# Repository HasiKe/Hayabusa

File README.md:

# Hayabusa

Eigenbau-Motorsteuerung und Umbauprojekte für die Suzuki Hayabusa der ersten
Generation (1999–2007).

Das Repository enthält die Elektronik des Umbaus: Schaltpläne und Layouts der
Steuergeräte, die Firmware, die Abstimmung und die Dokumentation dazu. Die
Speeduino-Firmware ist dabei der Ausgangspunkt, nicht das Ergebnis — Platinen,
Sensorik und die Motorrad-spezifischen Funktionen sind eigene Arbeit.

---

## Inhalt

| Pfad | Inhalt |
|---|---|
| [`hardware/ECU/`](hardware/ECU) | Steuergerät: Schaltplan, Layout, Fertigungsdaten, Gehäuse |
| [`speeduino/`](https://github.com/HasiKe/speeduino/tree/Hayabusa/ECU-R3) | Motorsteuerungs-Firmware und Sensor-Modul-Firmware, Submodul auf den eigenen Fork |
| [`hardware/exhaust-mic/`](hardware/exhaust-mic) | Zweikanalige Tonaufnahme von Motor und Auspuff |
| [`tune/`](tune) | TunerStudio-Projekt [`Hayabusa-R3`](tune/Hayabusa-R3) (generiert aus den Serienkennfeldern in `tune/setup/`) |
| [`docs/`](docs) | Dokumentation und Spezifikationen |

---

## Das Steuergerät

Ersetzt das Seriensteuergerät vollständig. Zweilagige Platine von rund
148 × 112 mm mit einem Teensy 4.1 als Rechenkern, Schaltplanstand
**Revision 3.0 (Entwurf)**.

### Leistungsteil

| Baustein | Aufgabe |
|---|---|
| MC33810 | Einspritzung und Zündung über SPI, vier Kanäle je Pfad |
| 4× ISL9V5036 | Zünd-IGBTs an den Gate-Treibern des MC33810 |
| 3× ZXMS6006 | Low-Side für Kraftstoffpumpe, Lüfter, Starter, Drehzahlmesser, FI-Lampe |
| 2× BTF3050TE | High-Side für Ladedrucksteller und Lambdaheizung, mit Stromfühler |
| DRV8434A | Schrittmotor für den Leerlaufsteller |

### Signalaufbereitung

| Baustein | Aufgabe |
|---|---|
| MAX9926 | Zwei Kanäle Induktivgeber für Kurbelwelle und Nockenwelle |
| TPIC8101 | Klopfsensor mit programmierbarem Bandpass und Integrator |
| LMV324 | Puffer für Lambda, Komparator für den Kippschalter |
| SP720 / BAV199 | Klemmung sämtlicher Sensoreingänge |

### Versorgung und Infrastruktur

| Baustein | Aufgabe |
|---|---|
| LM74700 + SQM120N06 | Verpolschutz als aktive Diode |
| TPS54360B | Abwärtswandler auf 5 V, automotive-tauglich |
| TPS3823 | Externer Watchdog, verriegelt bei Ausfall die Endstufen |
| W25Q32 | SPI-Flash als Kennfeldspeicher |
| MCP2562 | CAN zum Sensor-Modul und zum Cockpit |
| ADXL343 | Beschleunigungssensor, bestückt, softwareseitig ungenutzt |

Vollständige Pinbelegung, Kalibrierhinweise und die offenen Punkte der
Revision 3.0: **[HAYABUSA_ECU_R3.md](https://github.com/HasiKe/speeduino/blob/Hayabusa/ECU-R3/HAYABUSA_ECU_R3.md)**

---

## Firmware

Fork von [Speeduino](https://github.com/speeduino/speeduino), Branch
[`Hayabusa/ECU-R3`](https://github.com/HasiKe/speeduino/tree/Hayabusa/ECU-R3),
eingebunden als Submodul.

```bash
git submodule update --init
cd speeduino && pio run -e teensy41_hayabusa
```

In TunerStudio Board **57 „Gen1 Hayabusa ECU R3"** wählen.

Was über den Serienstand von Speeduino hinausgeht:

- **Vier umschaltbare Kennfeldsätze** für Kraftstoff, Zündung und Ladedruck.
  Auswahl beim Einschalten über Kupplung und Vollgas, Rückmeldung über
  FI-Lampe und Drehzahlmesser.
- **Klopfregelung** mit dem TPIC8101: Konfiguration über SPI,
  Integrationsfenster am Zündfunken, Auswertung über Speeduinos
  Zündrücknahme.
- **Externer Watchdog**, der nur bedient wird, solange die Hauptschleife
  läuft — bleibt sie hängen, fallen Einspritzung und Zündung ab.
- **Motorrad-Ein- und Ausgänge**: Neutral, Kupplung, Gangsensor,
  Kippschalter, FI-Lampe, Lambdaheizung.
- **Kanalzuordnung nach Zündfolge 1-2-4-3** am Serienstecker, der nach
  Zylindern belegt ist.
- **Kennfelder im SPI-Flash** statt in der EEPROM-Emulation des Teensy, die
  für vier Sätze zu klein ist.

---

## Sensor-Modul

Zweite Platine, 120 × 64 mm, eigener STM32G474. Nimmt der Motorsteuerung alles
ab, was langsam ist, und meldet es über CAN.

- vier Abgastemperaturen über MAX31855K-Thermoelementwandler
- Öldruck, Kraftstoffdruck, Abgasdruck, Öltemperatur
- zwei Wassertemperaturen im Ladeluftkühlerkreis
- Quickshifter-Geber
- Regelung des Ladeluftkühler-Lüfters, lokal und damit unabhängig vom CAN-Bus

Firmware, CAN-Protokoll und die Zuordnung zu Speeduinos Eingangskanälen:
[`speeduino/sensor-module/README.md`](https://github.com/HasiKe/speeduino/blob/Hayabusa/ECU-R3/sensor-module/README.md)

---

## Exhaust-Mic

Eigenständiges Projekt: zweikanalige Tonaufnahme von Motor- und
Auspuffgeräuschen. Zwei Mikrofonköpfe mit 135 dBSPL Grenzschalldruck an einem
24-bit-Stereo-ADC, aufgezeichnet von einem ESP32-S3 auf microSD, mit
Zeitstempeln zur Synchronisation mit Videomaterial.

Schaltpläne, Layout, Gehäuse und Firmware entstehen aus Python-Generatoren —
Pinbelegung und Netznamen stehen dadurch nur an einer Stelle.

Eigenes Repository, hier als Submodul eingebunden:
[HasiKe/Exhaust-Mic](https://github.com/HasiKe/Exhaust-Mic)

---

## Stand

| Bereich | Stand |
|---|---|
| Steuergerät, Schaltplan | Revision 3.0 im Entwurf, Revision 1 gefertigt |
| Steuergerät, Firmware | Läuft, auf aktuellem Speeduino-Stand |
| Sensor-Modul, Hardware | Revision 3.0 im Entwurf |
| Sensor-Modul, Firmware | Übersetzt, noch nicht am Fahrzeug erprobt |
| Exhaust-Mic | Schaltplan und Layout fertig, Fertigung offen |
| Grundabstimmung | Erststart-Tune erzeugt (`tune/Hayabusa-R3`), Motor damit noch nicht gelaufen |

Was vor dem ersten Start geprüft werden muss — Trigger-Winkel, Kalibrierungen,
Kanalzuordnung, Polarität des Kippschalters, Klopfschwellen — steht in
[`tune/Hayabusa-R3/README.md`](tune/Hayabusa-R3/README.md),
[HAYABUSA_ECU_R3.md](https://github.com/HasiKe/speeduino/blob/Hayabusa/ECU-R3/HAYABUSA_ECU_R3.md)
und im [README des Sensor-Moduls](https://github.com/HasiKe/speeduino/blob/Hayabusa/ECU-R3/sensor-module/README.md).

---

## Dokumentation

| Dokument | Inhalt |
|---|---|
| [HARDWARE.md](docs/HARDWARE.md) | Platinen, Steckerbelegung, mechanische Daten |
| [SOFTWARE.md](docs/SOFTWARE.md) | Firmware-Aufbau, Build, Codestruktur |
| [INSTALLATION.md](docs/INSTALLATION.md) | Einbau, Verkabelung, Inbetriebnahme |
| [TUNING.md](docs/TUNING.md) | Kennfelder, Kalibrierung, Abstimmung |
| [PROJECT_STRUCTURE.md](docs/PROJECT_STRUCTURE.md) | Aufbau des Repositories |
| [CHANGELOG.md](CHANGELOG.md) | Versionshistorie |

Externe Quellen: [Speeduino-Wiki](https://wiki.speeduino.com) ·
[Speeduino-Forum](https://speeduino.com/forum) ·
[TunerStudio](http://tunerstudio.com)

---

## Lizenz

Die Firmware im Submodul steht unter GPL v3, wie Speeduino selbst. Hardware
und Dokumentation stehen unter CC BY-SA 4.0. Fremdsoftware liegt nicht im
Repository, sondern wird bei Bedarf aus der jeweiligen Quelle geladen.

## Haftungsausschluss

Ein selbst gebautes Steuergerät greift in Zündung und Kraftstoffzufuhr ein.
Fehler darin führen zu Motorschaden oder zum Ausfall während der Fahrt. Der
Nachbau erfolgt auf eigene Verantwortung, und im Geltungsbereich der StVZO
erlischt mit solchen Eingriffen die Betriebserlaubnis, solange kein Gutachten
vorliegt.

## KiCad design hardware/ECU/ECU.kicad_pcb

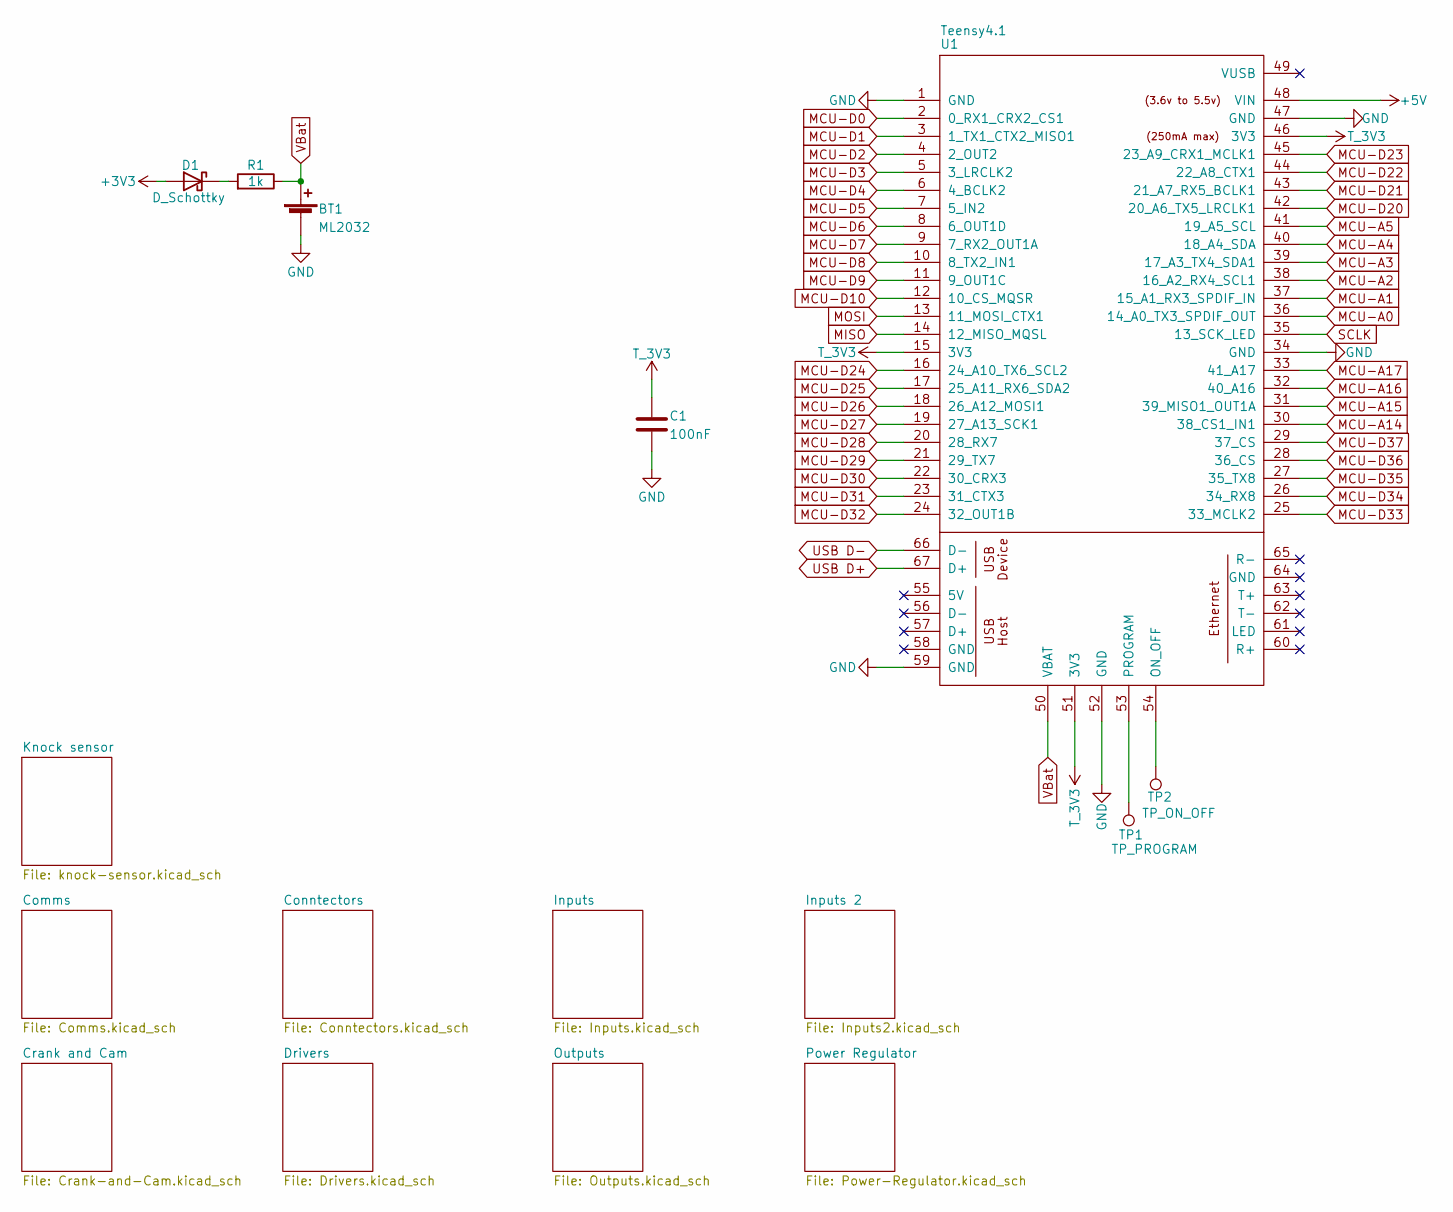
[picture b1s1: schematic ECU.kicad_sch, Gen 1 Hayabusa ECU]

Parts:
BT1: ML2032; BatteryHolder_Keystone_3034_1x20mm; Manufacturer_Part_Number 3034; Digikey Part Number 36-3034-ND
C1: 100nF; C_0805_2012Metric; Manufacturer_Part_Number CC0805KRX7R9BB104; Digikey Part Number 311-1140-1-ND
D1: D_Schottky; D_PowerDI-123; Manufacturer_Part_Number DFLS240-7; Digikey Part Number DFLS240-7DICT-ND
R1: 1k; R_0805_2012Metric; Manufacturer_Part_Number RC0805FR-071KL; Digikey Part Number 311-1.00KCRCT-ND
TP1: TP_PROGRAM; TestPoint_Pad_D1.5mm
TP2: TP_ON_OFF; TestPoint_Pad_D1.5mm
U1: Teensy4.1; Teensy41; Manufacturer_Part_Number DEV-16771; Digikey Part Number 1568-16771-ND

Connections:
+3V3: D1.2 (A); also elsewhere on the board
+5V: U1.48 (VIN); also elsewhere on the board
GND: BT1.2 (-), C1.2, U1.1 (GND), U1.34 (GND), U1.47 (GND), U1.52 (GND), U1.59 (GND); also elsewhere on the board
MC33810_1-CS: U1.12 (10_CS_MQSR); also elsewhere on the board
MCU-A0: U1.36 (14_A0_TX3_SPDIF_OUT); also elsewhere on the board
MCU-A1: U1.37 (15_A1_RX3_SPDIF_IN); also elsewhere on the board
MCU-A2: U1.38 (16_A2_RX4_SCL1); also elsewhere on the board
MCU-A3: U1.39 (17_A3_TX4_SDA1); also elsewhere on the board
MCU-A4: U1.40 (18_A4_SDA); also elsewhere on the board
MCU-A5: U1.41 (19_A5_SCL); also elsewhere on the board
MCU-A14: U1.30 (38_CS1_IN1); also elsewhere on the board
MCU-A15: U1.31 (39_MISO1_OUT1A); also elsewhere on the board
MCU-A16: U1.32 (40_A16); also elsewhere on the board
MCU-A17: U1.33 (41_A17); also elsewhere on the board
MCU-D0: U1.2 (0_RX1_CRX2_CS1); also elsewhere on the board
MCU-D1: U1.3 (1_TX1_CTX2_MISO1); also elsewhere on the board
MCU-D2: U1.4 (2_OUT2); also elsewhere on the board
MCU-D3: U1.5 (3_LRCLK2); also elsewhere on the board
MCU-D4: U1.6 (4_BCLK2); also elsewhere on the board
MCU-D5: U1.7 (5_IN2); also elsewhere on the board
MCU-D6: U1.8 (6_OUT1D); also elsewhere on the board
MCU-D7: U1.9 (7_RX2_OUT1A); also elsewhere on the board
MCU-D8: U1.10 (8_TX2_IN1); also elsewhere on the board
MCU-D9: U1.11 (9_OUT1C); also elsewhere on the board
MCU-D20: U1.42 (20_A6_TX5_LRCLK1); also elsewhere on the board
MCU-D21: U1.43 (21_A7_RX5_BCLK1); also elsewhere on the board
MCU-D22: U1.44 (22_A8_CTX1); also elsewhere on the board
MCU-D23: U1.45 (23_A9_CRX1_MCLK1); also elsewhere on the board
MCU-D24: U1.16 (24_A10_TX6_SCL2); also elsewhere on the board
MCU-D25: U1.17 (25_A11_RX6_SDA2); also elsewhere on the board
MCU-D26: U1.18 (26_A12_MOSI1); also elsewhere on the board
MCU-D27: U1.19 (27_A13_SCK1); also elsewhere on the board
MCU-D28: U1.20 (28_RX7); also elsewhere on the board
MCU-D29: U1.21 (29_TX7); also elsewhere on the board
MCU-D30: U1.22 (30_CRX3); also elsewhere on the board
MCU-D31: U1.23 (31_CTX3); also elsewhere on the board
MCU-D32: U1.24 (32_OUT1B); also elsewhere on the board
MCU-D33: U1.25 (33_MCLK2); also elsewhere on the board
MCU-D34: U1.26 (34_RX8); also elsewhere on the board
MCU-D35: U1.27 (35_TX8); also elsewhere on the board
MCU-D36: U1.28 (36_CS); also elsewhere on the board
MCU-D37: U1.29 (37_CS); also elsewhere on the board
MISO: U1.14 (12_MISO_MQSL); also elsewhere on the board
MOSI: U1.13 (11_MOSI_CTX1); also elsewhere on the board
unnamed: D1.1 (K), R1.2
unnamed: TP2.1 (1_1), U1.54 (ON_OFF)
unnamed: TP1.1 (1_1), U1.53 (PROGRAM)
SCLK: U1.35 (13_SCK_LED); also elsewhere on the board
T_3V3: C1.1, U1.15 (3V3), U1.46 (3V3), U1.51 (3V3)
USB D+: U1.67 (D+); also elsewhere on the board
USB D-: U1.66 (D-); also elsewhere on the board
VBat: BT1.1 (+), R1.1, U1.50 (VBAT)

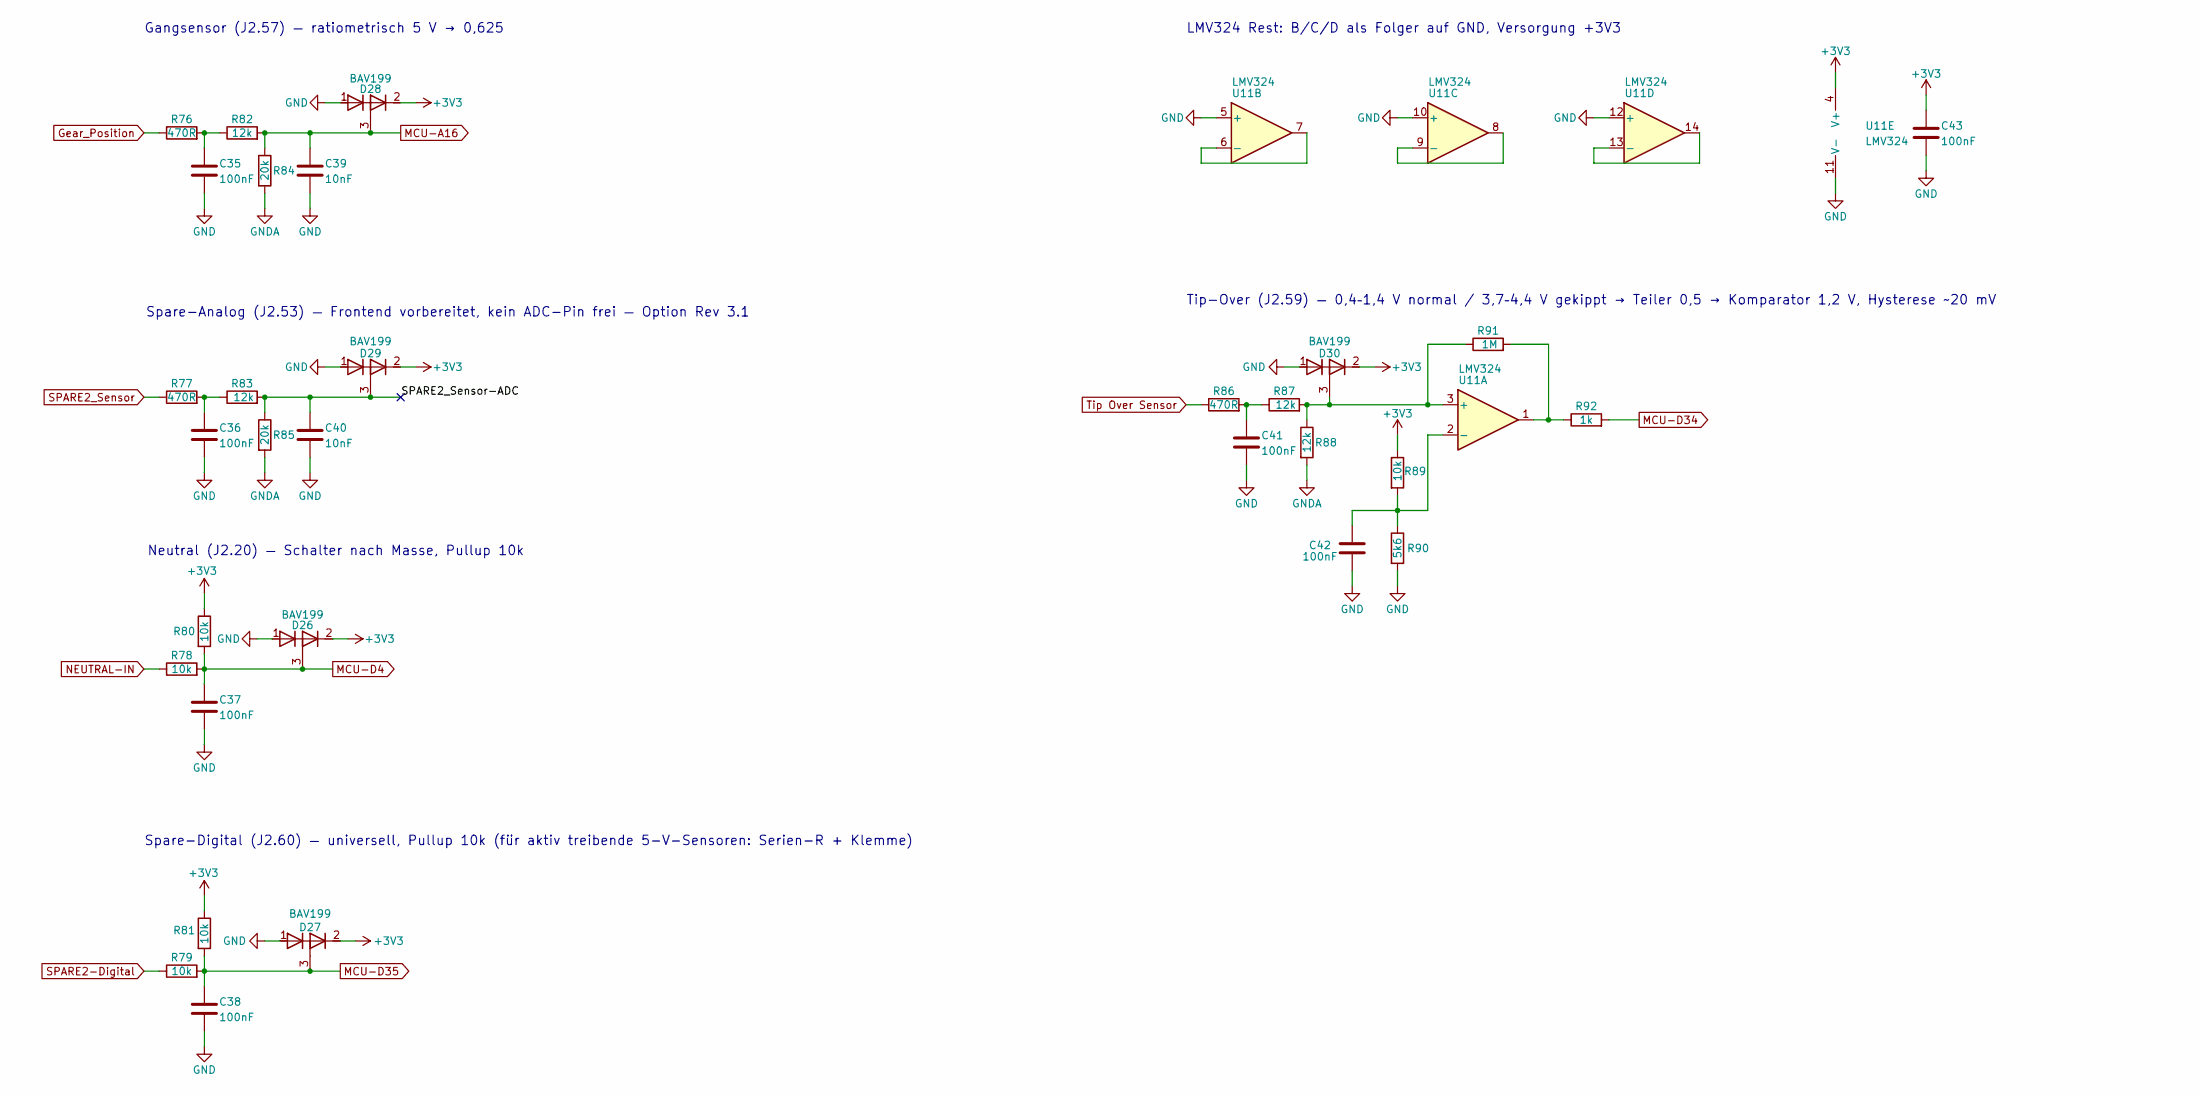
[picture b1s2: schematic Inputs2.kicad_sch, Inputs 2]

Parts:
C35, C36, C37, C38, C41, C42, C43: 100nF; C_0805_2012Metric; Manufacturer_Part_Number CC0805KRX7R9BB104; Digikey Part Number 311-1140-1-ND
C39, C40: 10nF; C_0805_2012Metric; Manufacturer_Part_Number CC0805KRX7R9BB103; Digikey Part Number 311-1136-1-ND
D26, D27, D28, D29, D30: BAV199; SOT-23; Manufacturer_Part_Number BAV199LT1G; Digikey Part Number BAV199LT1GOSCT-ND
R76, R77, R86: 470R; R_0805_2012Metric; Manufacturer_Part_Number RC0805FR-07470RL; Digikey Part Number 311-470CRCT-ND
R78, R79, R80, R81, R89: 10k; R_0805_2012Metric; Manufacturer_Part_Number RC0805FR-0710KL; Digikey Part Number 311-10.0KCRCT-ND
R82, R83, R87, R88: 12k; R_0805_2012Metric; Manufacturer_Part_Number RC0805FR-0712KL; Digikey Part Number 311-12.0KCRCT-ND
R84, R85: 20k; R_0805_2012Metric; Manufacturer_Part_Number RC0805FR-0720KL; Digikey Part Number 311-20.0KCRCT-ND
R90: 5k6; R_0805_2012Metric; Manufacturer_Part_Number RC0805FR-075K6L; Digikey Part Number 311-5.60KCRCT-ND
R91: 1M; R_0805_2012Metric; Manufacturer_Part_Number RC0805FR-071ML; Digikey Part Number 311-1.00MCRCT-ND
R92: 1k; R_0805_2012Metric; Manufacturer_Part_Number RC0805FR-071KL; Digikey Part Number 311-1.00KCRCT-ND
U11: LMV324; SOIC-14_3.9x8.7mm_P1.27mm; Manufacturer_Part_Number LMV324IDR; Digikey Part Number 296-9569-1-ND

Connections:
+3V3: C43.1, D26.2 (K2), D27.2 (K2), D28.2 (K2), D29.2 (K2), D30.2 (K2), R80.1, R81.1, R89.1, U11.4 (V+); also elsewhere on the board
/Inputs 2/SPARE2_Sensor-ADC: C40.1, D29.3 (K1A2), R83.2, R85.1
GND: C35.2, C36.2, C37.2, C38.2, C39.2, C40.2, C41.2, C42.2, C43.2, D26.1 (A1), D27.1 (A1), D28.1 (A1), D29.1 (A1), D30.1 (A1), R90.2, U11.5 (+), U11.10 (+), U11.11 (V-), U11.12 (+); also elsewhere on the board
GNDA: R84.2, R85.2, R88.2; also elsewhere on the board
Gear_Position: R76.1; also elsewhere on the board
MCU-A16: C39.1, D28.3 (K1A2), R82.2, R84.1; also elsewhere on the board
MCU-D4: C37.1, D26.3 (K1A2), R78.2, R80.2; also elsewhere on the board
MCU-D34: R92.2; also elsewhere on the board
MCU-D35: C38.1, D27.3 (K1A2), R79.2, R81.2; also elsewhere on the board
NEUTRAL-IN: R78.1; also elsewhere on the board
unnamed: C35.1, R76.2, R82.1
unnamed: C36.1, R77.2, R83.1
unnamed: C41.1, R86.2, R87.1
unnamed: D30.3 (K1A2), R87.2, R88.1, R91.1, U11.3 (+)
unnamed: R91.2, R92.1, U11.1
unnamed: C42.1, R89.2, R90.1, U11.2 (-)
unnamed: U11.6 (-), U11.7
unnamed: U11.8, U11.9 (-)
unnamed: U11.13 (-), U11.14
SPARE2-Digital: R79.1; also elsewhere on the board
SPARE2_Sensor: R77.1; also elsewhere on the board
Tip Over Sensor: R86.1; also elsewhere on the board

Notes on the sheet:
Spare-Digital (J2.60) — universell, Pullup 10k (für aktiv treibende 5-V-Sensoren: Serien-R + Klemme)
Spare-Analog (J2.53) — Frontend vorbereitet, kein ADC-Pin frei — Option Rev 3.1
Tip-Over (J2.59) — 0,4–1,4 V normal / 3,7–4,4 V gekippt → Teiler 0,5 → Komparator 1,2 V, Hysterese ~20 mV
LMV324 Rest: B/C/D als Folger auf GND, Versorgung +3V3
Gangsensor (J2.57) — ratiometrisch 5 V → 0,625
Neutral (J2.20) — Schalter nach Masse, Pullup 10k

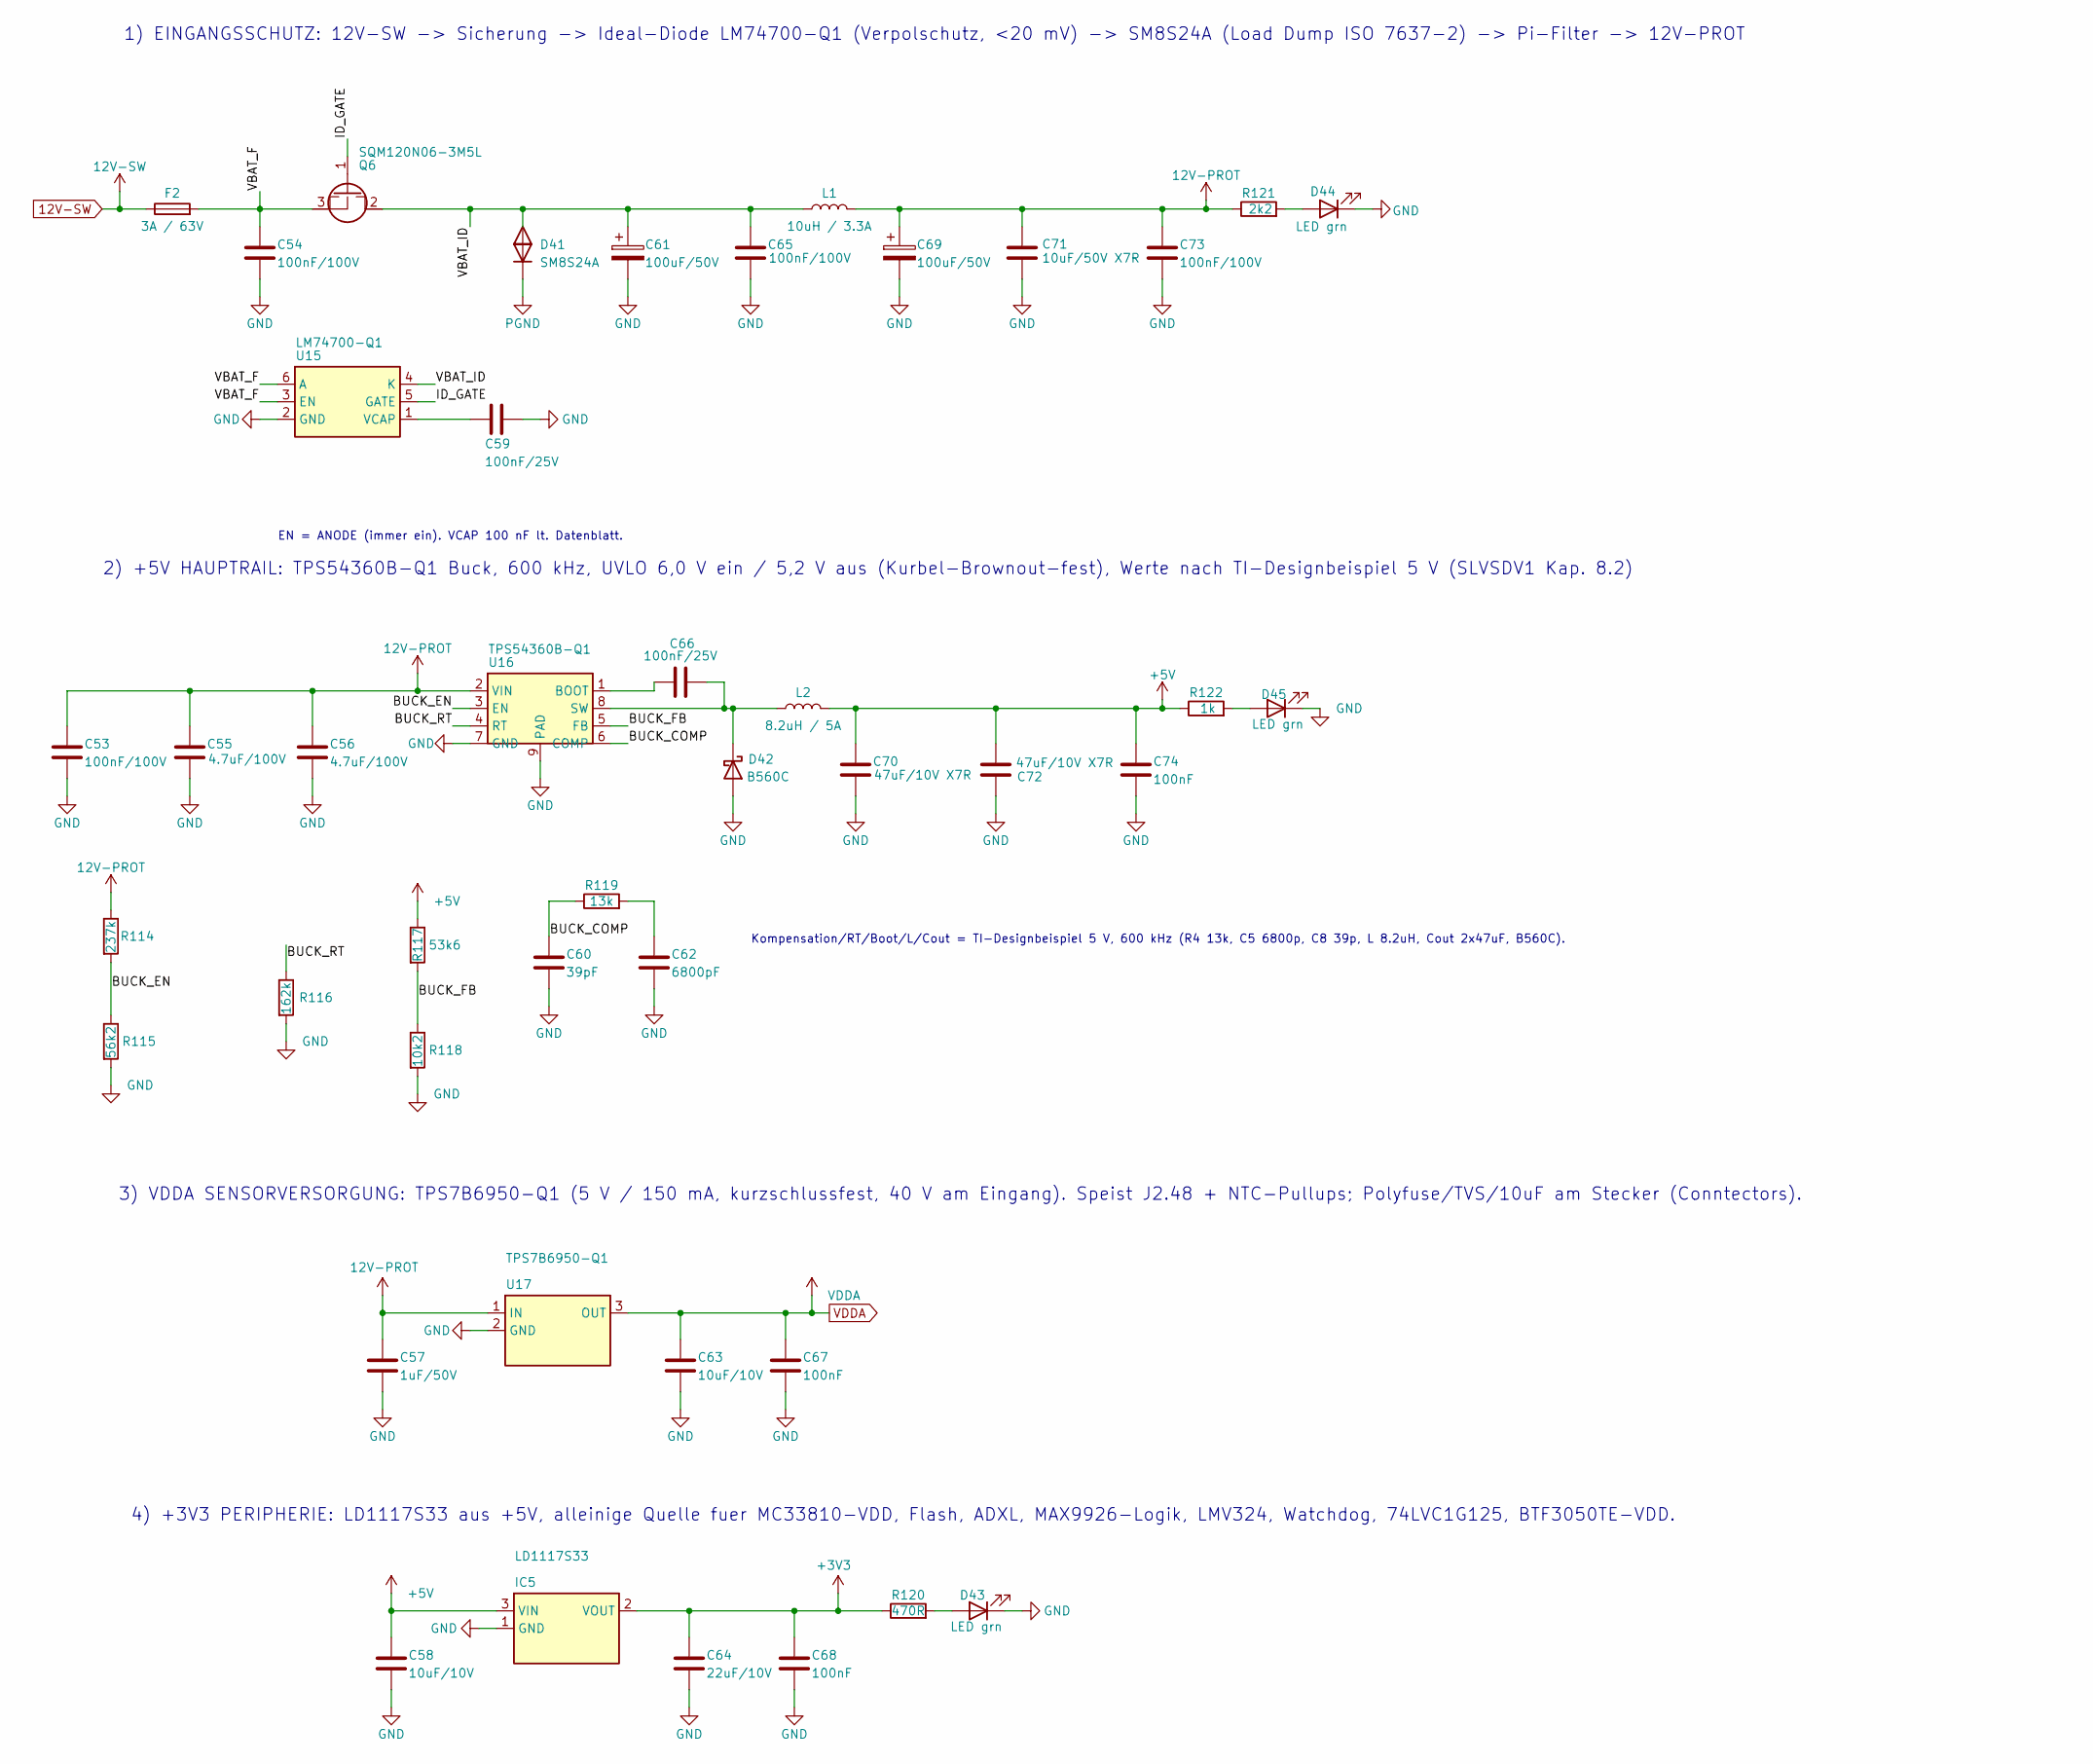
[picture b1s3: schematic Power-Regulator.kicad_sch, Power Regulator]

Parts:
C53, C54, C65, C73: 100nF/100V; C_1210_3225Metric; Manufacturer_Part_Number C1210C104K1RACTU; Digikey Part Number 399-C1210C104K1RACTUCT-ND
C55, C56: 4.7uF/100V; C_1210_3225Metric; Manufacturer_Part_Number C3225X7S2A475K200AB; Digikey Part Number 445-6042-1-ND
C57: 1uF/50V; C_0805_2012Metric; Manufacturer_Part_Number CC0805KKX7R9BB105; Digikey Part Number 311-1886-1-ND
C58, C63: 10uF/10V; C_0805_2012Metric; Manufacturer_Part_Number CL21A106KPFNNNE; Digikey Part Number 1276-1052-1-ND
C59, C66: 100nF/25V; C_0805_2012Metric; Manufacturer_Part_Number CC0805KRX7R9BB104; Digikey Part Number 311-1140-1-ND
C60: 39pF; C_0805_2012Metric; Manufacturer_Part_Number CC0805JRNPO9BN390; Digikey Part Number 311-1106-1-ND
C61, C69: 100uF/50V; CP_Elec_8x10; Manufacturer_Part_Number EEE-FK1H101GP; Digikey Part Number PCE4323CT-ND
C62: 6800pF; C_0805_2012Metric; Manufacturer_Part_Number CC0805KRX7R9BB682; Digikey Part Number 311-1135-1-ND
C64: 22uF/10V; C_1210_3225Metric; Manufacturer_Part_Number GRM32ER71A226KE20L; Digikey Part Number 490-1876-1-ND
C67, C68, C74: 100nF; C_0805_2012Metric; Manufacturer_Part_Number CC0805KRX7R9BB104; Digikey Part Number 311-1140-1-ND
C70, C72: 47uF/10V X7R; C_1210_3225Metric; Manufacturer_Part_Number CL32A476KOJNNNE; Digikey Part Number 1276-3376-1-ND
C71: 10uF/50V X7R; C_1210_3225Metric; Manufacturer_Part_Number C3225X7R1H106K250AC; Digikey Part Number 445-C3225X7R1H106K250ACCT-ND
D41: SM8S24A; D_DO-218AB; Manufacturer_Part_Number SM8S24A; Digikey Part Number 1655-SM8S24ACT-ND
D42: B560C; D_SMC; Manufacturer_Part_Number B560C-13-F; Digikey Part Number B560C-FDICT-ND
D43, D44, D45: LED grn; LED_0805_2012Metric; Manufacturer_Part_Number LTST-C170GKT; Digikey Part Number 160-1179-1-ND
F2: 3A / 63V; Fuse_1206_3216Metric; Manufacturer_Part_Number 0483003.DR; Digikey Part Number 18-0483003.DRCT-ND
IC5: LD1117S33; SOT-223-3_TabPin2; Manufacturer_Part_Number LD1117S33CTR; Digikey Part Number 497-1241-1-ND
L1: 10uH / 3.3A; L_Bourns_SRR1260; Manufacturer_Part_Number SRR1260-100M; Digikey Part Number SRR1260-100MCT-ND
L2: 8.2uH / 5A; L_Bourns_SRR1260; Manufacturer_Part_Number SRR1260A-8R2Y; Digikey Part Number SRR1260A-8R2YCT-ND
Q6: SQM120N06-3M5L; TO-263-2; Manufacturer_Part_Number SQM120N06-3M5L_GE3; Digikey Part Number SQM120N06-3M5L_GE3CT-ND
R114: 237k; R_0805_2012Metric; Manufacturer_Part_Number RC0805FR-07237KL; Digikey Part Number 311-237KCRCT-ND
R115: 56k2; R_0805_2012Metric; Manufacturer_Part_Number RC0805FR-0756K2L; Digikey Part Number 311-56.2KCRCT-ND
R116: 162k; R_0805_2012Metric; Manufacturer_Part_Number RC0805FR-07162KL; Digikey Part Number 311-162KCRCT-ND
R117: 53k6; R_0805_2012Metric; Manufacturer_Part_Number RC0805FR-0753K6L; Digikey Part Number 311-53.6KCRCT-ND
R118: 10k2; R_0805_2012Metric; Manufacturer_Part_Number RC0805FR-0710K2L; Digikey Part Number 311-10.2KCRCT-ND
R119: 13k; R_0805_2012Metric; Manufacturer_Part_Number RC0805FR-0713KL; Digikey Part Number 311-13.0KCRCT-ND
R120: 470R; R_0805_2012Metric; Manufacturer_Part_Number RC0805FR-07470RL; Digikey Part Number 311-470CRCT-ND
R121: 2k2; R_0805_2012Metric; Manufacturer_Part_Number RC0805FR-072K2L; Digikey Part Number 311-2.20KCRCT-ND
R122: 1k; R_0805_2012Metric; Manufacturer_Part_Number RC0805FR-071KL; Digikey Part Number 311-1.00KCRCT-ND
U15: LM74700-Q1; SOT-23-6; Manufacturer_Part_Number LM74700QDBVRQ1; Digikey Part Number 296-LM74700QDBVRQ1CT-ND
U16: TPS54360B-Q1; HSOP-8-1EP_3.9x4.9mm_P1.27mm_EP2.41x3.1mm_ThermalVias; Manufacturer_Part_Number TPS54360BQDDARQ1; Digikey Part Number 296-46985-1-ND
U17: TPS7B6950-Q1; SOT-223-3_TabPin2; Manufacturer_Part_Number TPS7B6950QDCYRQ1; Digikey Part Number 296-40985-1-ND

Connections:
12V-PROT: C53.1, C55.1, C56.1, C57.1, C69.1, C71.1, C73.1, L1.2, R114.1, R121.1, U16.2 (VIN), U17.1 (IN); also elsewhere on the board
12V-SW: F2.1; also elsewhere on the board
+3V3: C64.1, C68.1, IC5.2 (VOUT), R120.1; also elsewhere on the board
+5V: C58.1, C70.1, C72.1, C74.1, IC5.3 (VIN), L2.2, R117.1, R122.1; also elsewhere on the board
/Power Regulator/BUCK_COMP: C60.1, R119.1, U16.6 (COMP)
/Power Regulator/BUCK_EN: R114.2, R115.1, U16.3 (EN)
/Power Regulator/BUCK_FB: R117.2, R118.1, U16.5 (FB)
/Power Regulator/BUCK_RT: R116.1, U16.4 (RT)
/Power Regulator/ID_GATE: Q6.1 (G), U15.5 (GATE)
/Power Regulator/VBAT_F: C54.1, F2.2, Q6.3 (S), U15.3 (EN), U15.6 (A)
/Power Regulator/VBAT_ID: C61.1, C65.1, D41.1, L1.1, Q6.2 (D), U15.4 (K)
GND: C53.2, C54.2, C55.2, C56.2, C57.2, C58.2, C59.2, C60.2, C61.2, C62.2, C63.2, C64.2, C65.2, C67.2, C68.2, C69.2, C70.2, C71.2, C72.2, C73.2, C74.2, D42.2 (A), D43.1 (K), D44.1 (K), D45.1 (K), IC5.1 (GND), R115.2, R116.2, R118.2, U15.2 (GND), U16.7 (GND), U16.9 (PAD), U17.2 (GND); also elsewhere on the board
unnamed: C62.1, R119.2
unnamed: C66.2, D42.1 (K), L2.1, U16.8 (SW)
unnamed: D43.2 (A), R120.2
unnamed: D44.2 (A), R121.2
unnamed: D45.2 (A), R122.2
unnamed: C59.1, U15.1 (VCAP)
unnamed: C66.1, U16.1 (BOOT)
PGND: D41.2; also elsewhere on the board
VDDA: C63.1, C67.1, U17.3 (OUT); also elsewhere on the board

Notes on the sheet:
EN = ANODE (immer ein). VCAP 100 nF lt. Datenblatt.
1) EINGANGSSCHUTZ: 12V-SW -> Sicherung -> Ideal-Diode LM74700-Q1 (Verpolschutz, <20 mV) -> SM8S24A (Load Dump ISO 7637-2) -> Pi-Filter -> 12V-PROT
2) +5V HAUPTRAIL: TPS54360B-Q1 Buck, 600 kHz, UVLO 6,0 V ein / 5,2 V aus (Kurbel-Brownout-fest), Werte nach TI-Designbeispiel 5 V (SLVSDV1 Kap. 8.2)
3) VDDA SENSORVERSORGUNG: TPS7B6950-Q1 (5 V / 150 mA, kurzschlussfest, 40 V am Eingang). Speist J2.48 + NTC-Pullups; Polyfuse/TVS/10uF am Stecker (Conntectors).
Kompensation/RT/Boot/L/Cout = TI-Designbeispiel 5 V, 600 kHz (R4 13k, C5 6800p, C8 39p, L 8.2uH, Cout 2x47uF, B560C).
4) +3V3 PERIPHERIE: LD1117S33 aus +5V, alleinige Quelle fuer MC33810-VDD, Flash, ADXL, MAX9926-Logik, LMV324, Watchdog, 74LVC1G125, BTF3050TE-VDD.

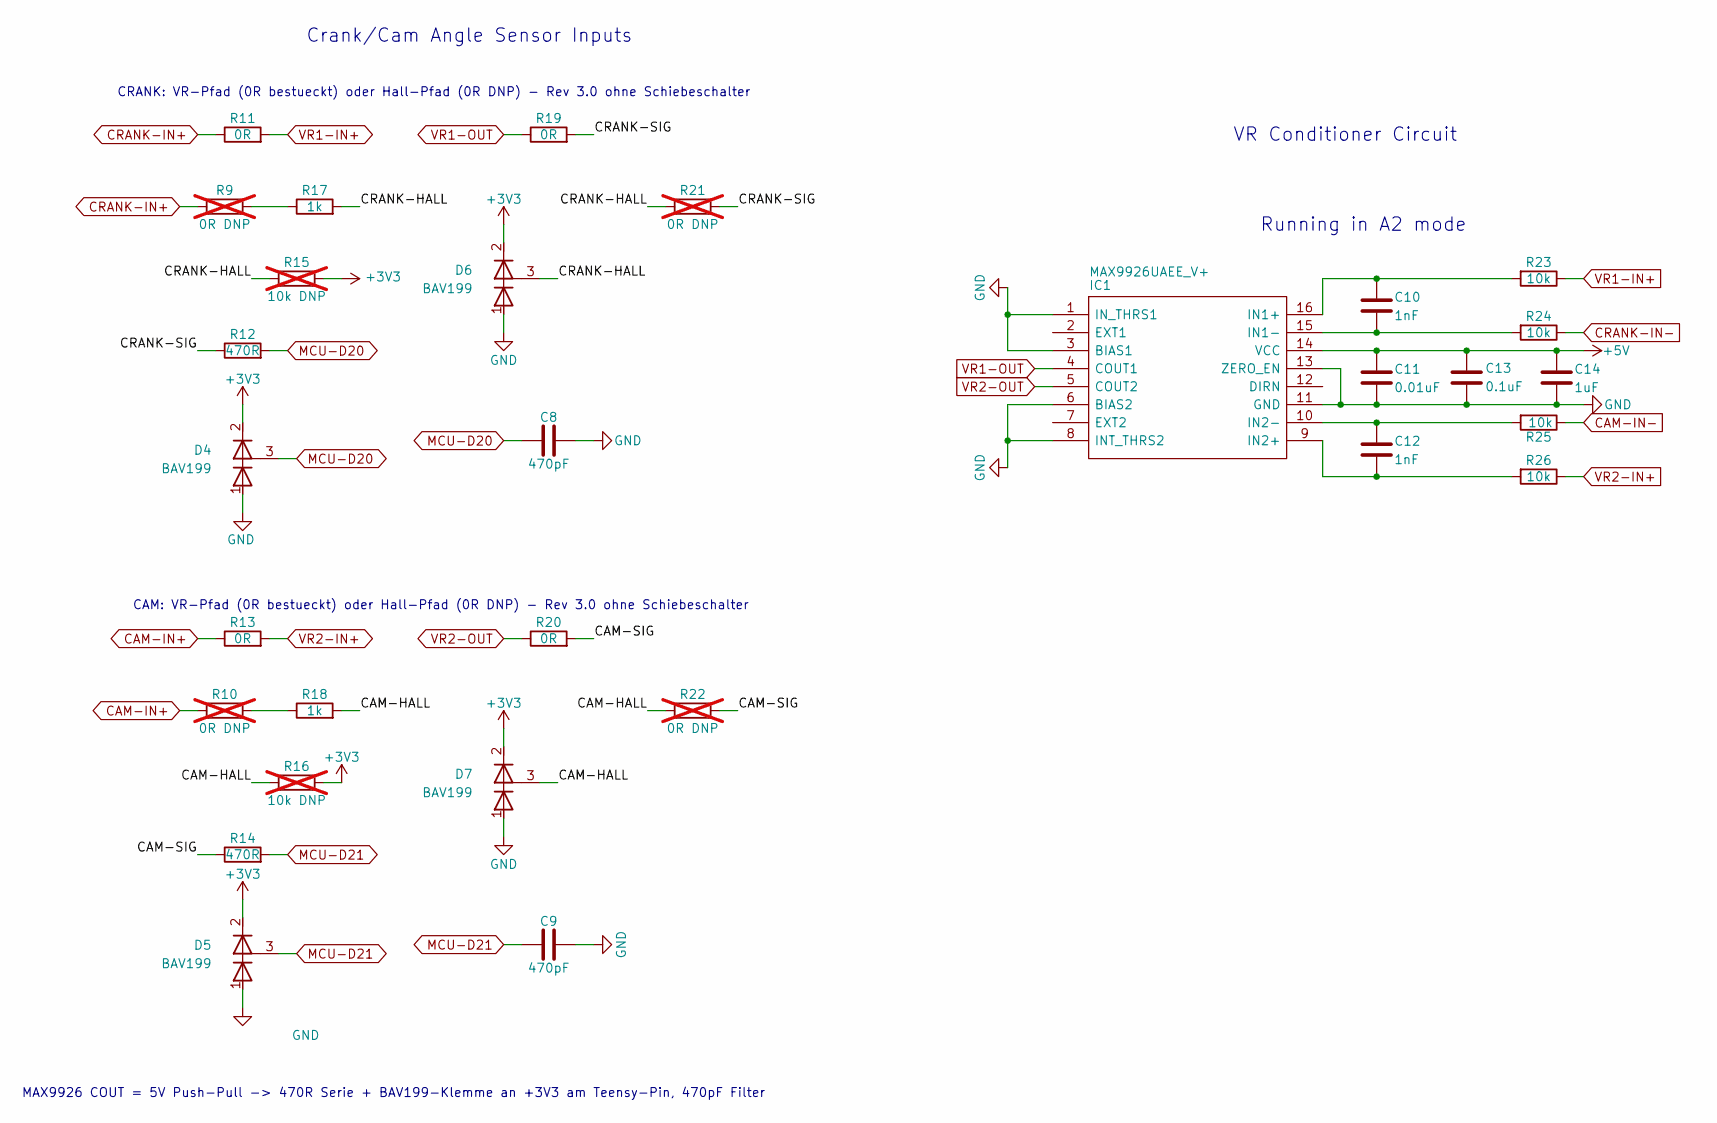
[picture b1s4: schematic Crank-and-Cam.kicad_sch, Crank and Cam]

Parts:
C8, C9: 470pF; C_0805_2012Metric; Manufacturer_Part_Number CC0805KRX7R9BB471; Digikey Part Number 311-1124-1-ND
C10, C12: 1nF; C_0805_2012Metric; Manufacturer_Part_Number C0805C102J5HACAUTO; Digikey Part Number 399-16591-1-ND
C11: 0.01uF; C_0805_2012Metric; Manufacturer_Part_Number CC0805KRX7R9BB103; Digikey Part Number 311-1136-1-ND
C13: 0.1uF; C_0805_2012Metric; Manufacturer_Part_Number CC0805KRX7R9BB104; Digikey Part Number 311-1140-1-ND
C14: 1uF; C_0805_2012Metric; Manufacturer_Part_Number CC0805KKX7R7BB105; Digikey Part Number 311-1365-1-ND
D4, D5, D6, D7: BAV199; SOT-23; Manufacturer_Part_Number BAV199LT1G; Digikey Part Number BAV199LT1GOSCT-ND
IC1: MAX9926UAEE_V+; QSOP-16_3.9x4.9mm_P0.635mm; Manufacturer_Part_Number MAX9926UAEE/V+; Mouser Part Number 700-MAX9926UAEE/V+
R9, R10, R21, R22: 0R DNP; R_0805_2012Metric; Manufacturer_Part_Number RC0805JR-070RL; Digikey Part Number 311-0.0ARCT-ND; not fitted
R11, R13, R19, R20: 0R; R_0805_2012Metric; Manufacturer_Part_Number RC0805JR-070RL; Digikey Part Number 311-0.0ARCT-ND
R12, R14: 470R; R_0805_2012Metric; Manufacturer_Part_Number RC0805FR-07470RL; Digikey Part Number 311-470CRCT-ND
R15, R16: 10k DNP; R_0805_2012Metric; Manufacturer_Part_Number RC0805FR-0710KL; Digikey Part Number 311-10.0KCRCT-ND; not fitted
R17, R18: 1k; R_0805_2012Metric; Manufacturer_Part_Number RC0805FR-071KL; Digikey Part Number 311-1.00KCRCT-ND
R23, R24, R25, R26: 10k; R_1206_3216Metric; Manufacturer_Part_Number RC1206FR-7W10KL; Digikey Part Number 13-RC1206FR-7W10KLTR-ND

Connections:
+3V3: D4.2 (K2), D5.2 (K2), D6.2 (K2), D7.2 (K2), R15.2, R16.2; also elsewhere on the board
+5V: C11.1, C13.1, C14.1, IC1.14 (VCC); also elsewhere on the board
/Crank and Cam/CAM-HALL: D7.3 (K1A2), R16.1, R18.2, R22.1
/Crank and Cam/CAM-SIG: R14.1, R20.2, R22.2
/Crank and Cam/CRANK-HALL: D6.3 (K1A2), R15.1, R17.2, R21.1
/Crank and Cam/CRANK-SIG: R12.1, R19.2, R21.2
CAM-IN+: R10.1, R13.1; also elsewhere on the board
CAM-IN-: R25.1; also elsewhere on the board
CRANK-IN+: R9.1, R11.1; also elsewhere on the board
CRANK-IN-: R24.1; also elsewhere on the board
GND: C8.2, C9.2, C11.2, C13.2, C14.2, D4.1 (A1), D5.1 (A1), D6.1 (A1), D7.1 (A1), IC1.1 (IN_THRS1), IC1.3 (BIAS1), IC1.6 (BIAS2), IC1.8 (INT_THRS2), IC1.11 (GND), IC1.13 (ZERO_EN); also elsewhere on the board
MCU-D20: C8.1, D4.3 (K1A2), R12.2; also elsewhere on the board
MCU-D21: C9.1, D5.3 (K1A2), R14.2; also elsewhere on the board
unnamed: C10.1, IC1.16 (IN1+), R23.2
unnamed: C10.2, IC1.15 (IN1-), R24.2
unnamed: C12.2, IC1.9 (IN2+), R26.2
unnamed: C12.1, IC1.10 (IN2-), R25.2
unnamed: R10.2, R18.1
unnamed: R9.2, R17.1
VR1-IN+: R11.2, R23.1
VR1-OUT: IC1.4 (COUT1), R19.1
VR2-IN+: R13.2, R26.1
VR2-OUT: IC1.5 (COUT2), R20.1

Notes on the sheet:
CRANK: VR-Pfad (0R bestueckt) oder Hall-Pfad (0R DNP) - Rev 3.0 ohne Schiebeschalter
VR Conditioner Circuit
Crank/Cam Angle Sensor Inputs
Running in A2 mode
MAX9926 COUT = 5V Push-Pull -> 470R Serie + BAV199-Klemme an +3V3 am Teensy-Pin, 470pF Filter
CAM: VR-Pfad (0R bestueckt) oder Hall-Pfad (0R DNP) - Rev 3.0 ohne Schiebeschalter
